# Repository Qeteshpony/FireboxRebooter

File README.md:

# FireboxRebooter
Rebooting a device that refuses to reboot

This piece of software, together with the hardware in this repository, allows automatic rebooting of a modified Watchguard Firebox M400 or M500 when the normal reboot doesn't work anymore. 

See https://electronics.qetesh.de/firebox-rebooter/ for details!

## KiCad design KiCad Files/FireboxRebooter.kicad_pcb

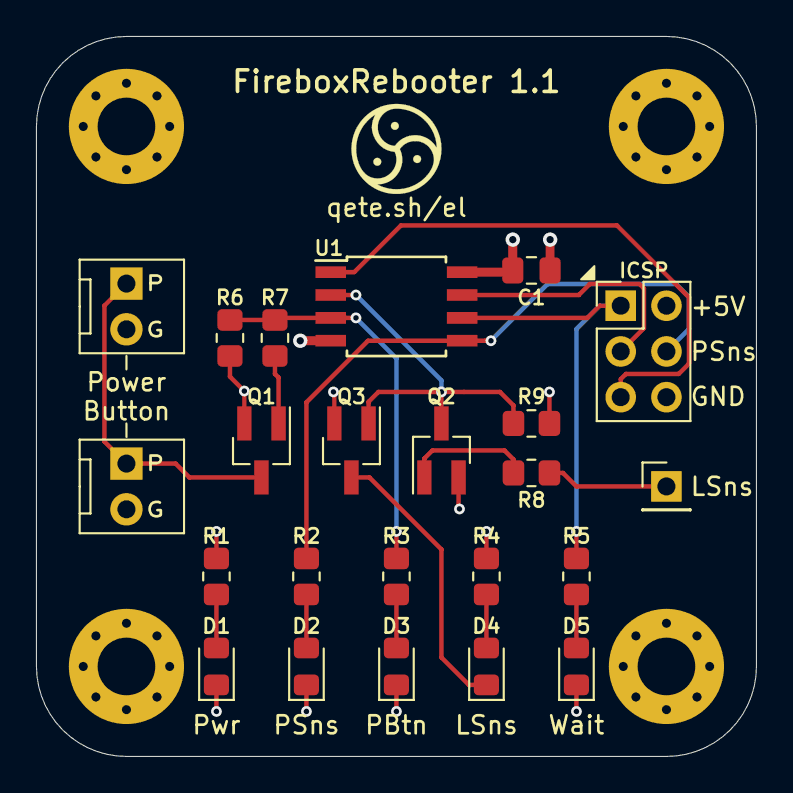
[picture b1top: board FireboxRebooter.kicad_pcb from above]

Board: 4 copper layers, 40.0 x 40.0 mm, 27 parts (0 on the bottom side), 18 nets.

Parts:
C1: 100nF; C_0805_2012Metric_Pad1.18x1.45mm_HandSolder
D1: PWR; LED_0805_2012Metric_Pad1.15x1.40mm_HandSolder
D2: PWR_SENSE; LED_0805_2012Metric_Pad1.15x1.40mm_HandSolder
D3: PWR_BTN; LED_0805_2012Metric_Pad1.15x1.40mm_HandSolder
D4: LED_SENSE; LED_0805_2012Metric_Pad1.15x1.40mm_HandSolder
D5: LED_WAIT; LED_0805_2012Metric_Pad1.15x1.40mm_HandSolder
H1, H2, H3, H4: MH; MountingHole_3.2mm_M3_Pad_Via
J1: ICSP; PinHeader_2x03_P2.54mm_Vertical
J2: LED_SENSE; PinHeader_1x01_P2.54mm_Vertical
J3: MB_PWRBTN; Wurth_WR-WTB_2.54mm_2Pin
J4: REAR_PWRBTN; Wurth_WR-WTB_2.54mm_2Pin
Q1, Q2, Q3: Si2302; SOT-23_Handsoldering
R1, R2, R3, R4, R5: 1k5; R_0805_2012Metric_Pad1.20x1.40mm_HandSolder
R6, R9: 10k; R_0805_2012Metric_Pad1.20x1.40mm_HandSolder
R7, R8: 1k; R_0805_2012Metric_Pad1.20x1.40mm_HandSolder
U1: ATtiny45-20SU; SOIJ-8_5.3x5.3mm_P1.27mm

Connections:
+5V: C1.1, J1.2, R1.2, R4.2, R9.2, U1.8
/LED_IN: J2.1, R8.2
/LED_SENSE: Q2.3, Q3.1, R9.1, U1.2
/LED_SENSE_LED: D4.1, Q3.3
/MISO: J1.1, R5.2, U1.6
/PWR_BTIN_N: J3.1, J4.1, Q1.3
/PWR_BTN: R3.2, R6.2, R7.2, U1.3
/PWR_SENSE: J1.4, R2.2, U1.5
/SCK: J1.3, U1.7
/~RESET: J1.5, U1.1
GND: C1.2, D1.1, D2.1, D3.1, D5.1, H1.1, H2.1, H3.1, H4.1, J1.6, J3.2, J4.2, Q1.2, Q2.2, Q3.2, R6.1, U1.4
unnamed: D1.2, R1.1
unnamed: D2.2, R2.1
unnamed: D3.2, R3.1
unnamed: D4.2, R4.1
unnamed: D5.2, R5.1
unnamed: Q1.1, R7.1
unnamed: Q2.1, R8.1

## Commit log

2022-01-05 Add KiCad Files
2022-01-05 Create LICENSE
2022-01-05 Hardware Version 1.1
    Fixed a little mistake
